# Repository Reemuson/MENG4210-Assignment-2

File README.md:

<h1 align="center">INPUT PROTECTION</h1>

<p align="center" width="100%">
  
</p>

***

<p align="center">
  
&nbsp; &nbsp; &nbsp; &nbsp;
  
</p>

***

## SPECIFICATIONS

| Parameter | Value | 
| --- | --- |
| Dimensions | 50.0 × 50.0 mm |

***

## DIRECTORY STRUCTURE

    .
    ├─ Computations       # Misc calculations
    ├─ HTML               # HTML files for generated webpage
    ├─ Images             # Pictures and renders
    │
    ├─ kibot_resources    # External resources for KiBot
    │  ├─ colors          # Color theme for KiCad
    │  ├─ fonts           # Fonts used in the project
    │  ├─ scripts         # External scripts used with KiBot
    │  └─ templates       # Templates for KiBot generated reports
    │
    ├─ kibot_yaml         # KiBot YAML config files
    ├─ KiRI               # KiRI (PCB diff viewer) files
    │
    ├─ lib                # KiCad footprint and symbol libraries
    │  ├─ 3d_models       # Component 3D models
    │  ├─ lib_fp          # Footprint libraries
    │  └─ lib_sym         # Symbol libraries
    │
    ├─ Logos              # Logos
    │
    ├─ Manufacturing      # Assembly and fabrication documents
    │  ├─ Assembly        # Assembly documents (BoM, pos, notes)
    │  │
    │  └─ Fabrication     # Fabrication documents (ZIP, notes)
    │     ├─ Drill Tables # CSV drill tables
    │     └─ Gerbers      # Gerbers
    │
    ├─ Report             # Reports for ERC/DRC
    ├─ Schematic          # PDF of schematic
    ├─ Templates          # Title block templates
    ├─ Testing
    │  └─ Testpoints      # Testpoints tables      
    │
    └─ Variants           # Outputs for assembly variants

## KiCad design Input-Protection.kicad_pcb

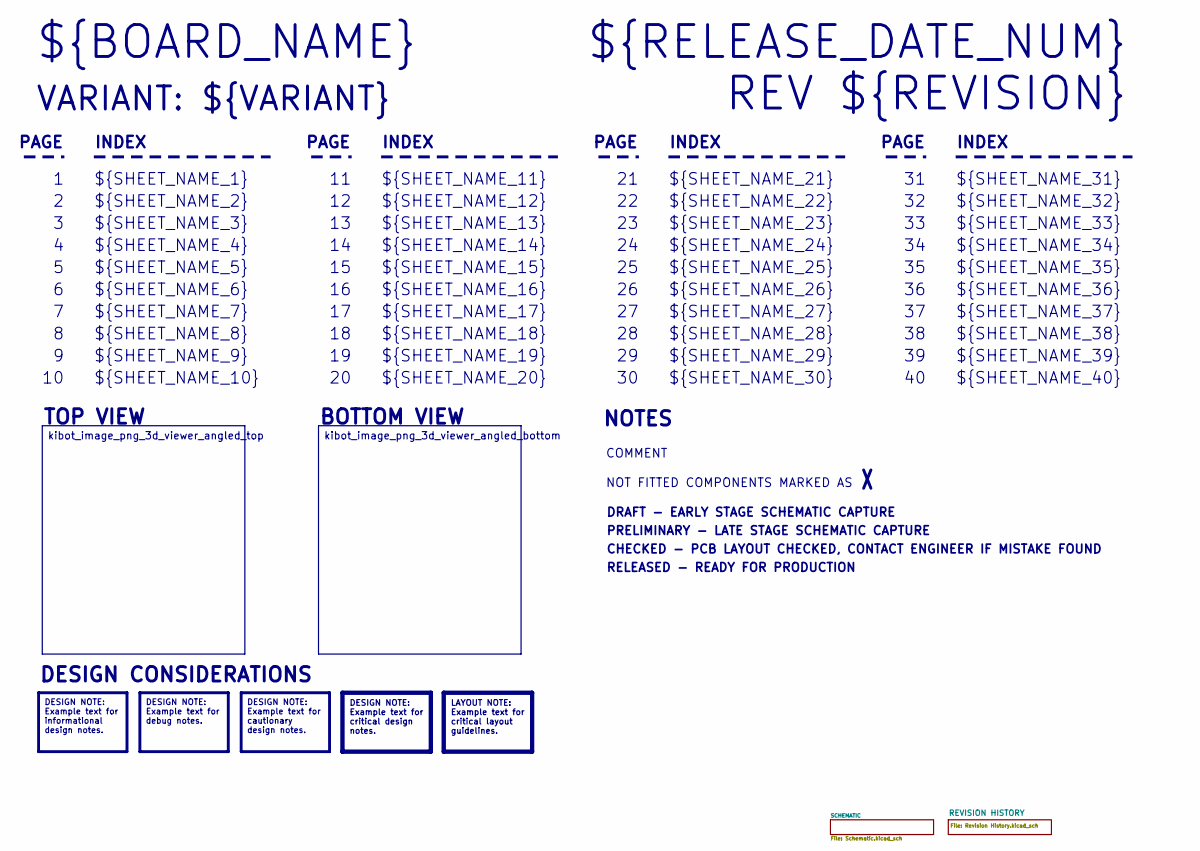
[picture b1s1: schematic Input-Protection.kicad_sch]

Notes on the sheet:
VARIANT: ${VARIANT}
${SHEET_NAME_24}
INDEX
PAGE
${SHEET_NAME_22}
DRAFT - EARLY STAGE SCHEMATIC CAPTURE
${SHEET_NAME_12}
${SHEET_NAME_8}
${SHEET_NAME_2}
${SHEET_NAME_5}
${SHEET_NAME_20}
${SHEET_NAME_23}
${RELEASE_DATE_NUM}
${SHEET_NAME_35}
${SHEET_NAME_11}
CHECKED - PCB LAYOUT CHECKED, CONTACT ENGINEER IF MISTAKE FOUND
${SHEET_NAME_6}
${SHEET_NAME_37}
NOT FITTED COMPONENTS MARKED AS
${SHEET_NAME_26}
${SHEET_NAME_36}
REV ${REVISION}
${SHEET_NAME_15}
BOTTOM VIEW
${SHEET_NAME_14}
${SHEET_NAME_21}
${SHEET_NAME_17}
${SHEET_NAME_18}
${SHEET_NAME_7}
${SHEET_NAME_31}
${BOARD_NAME}
NOTES
${SHEET_NAME_40}
${SHEET_NAME_39}
${SHEET_NAME_32}
${SHEET_NAME_1}
${SHEET_NAME_9}
${SHEET_NAME_38}
${SHEET_NAME_29}
RELEASED - READY FOR PRODUCTION

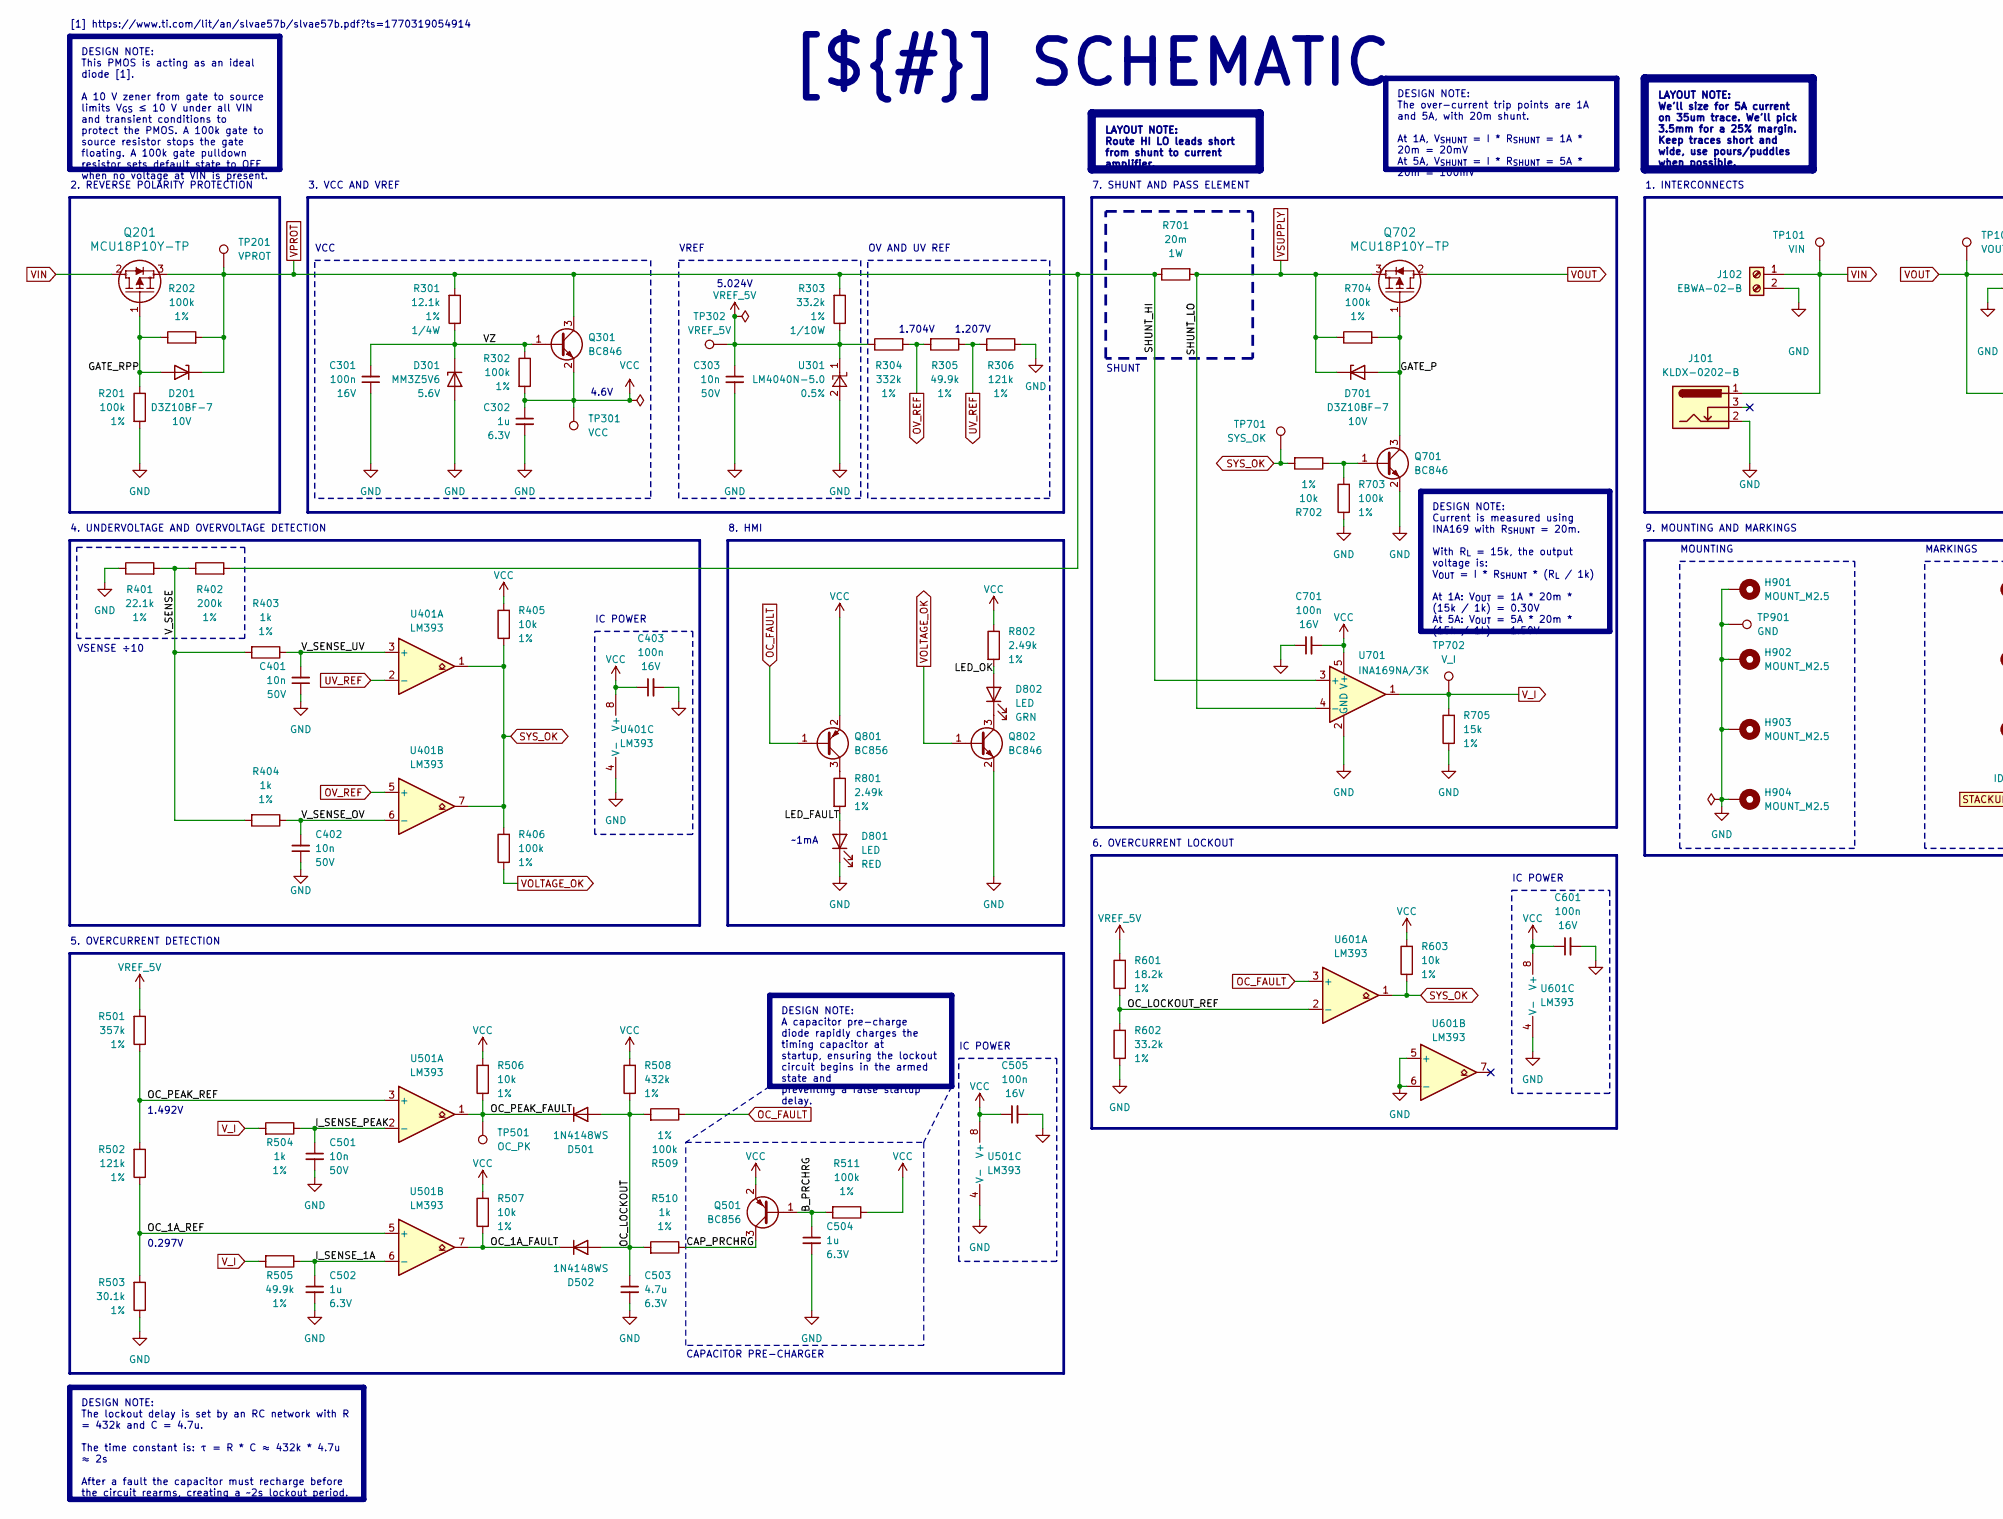
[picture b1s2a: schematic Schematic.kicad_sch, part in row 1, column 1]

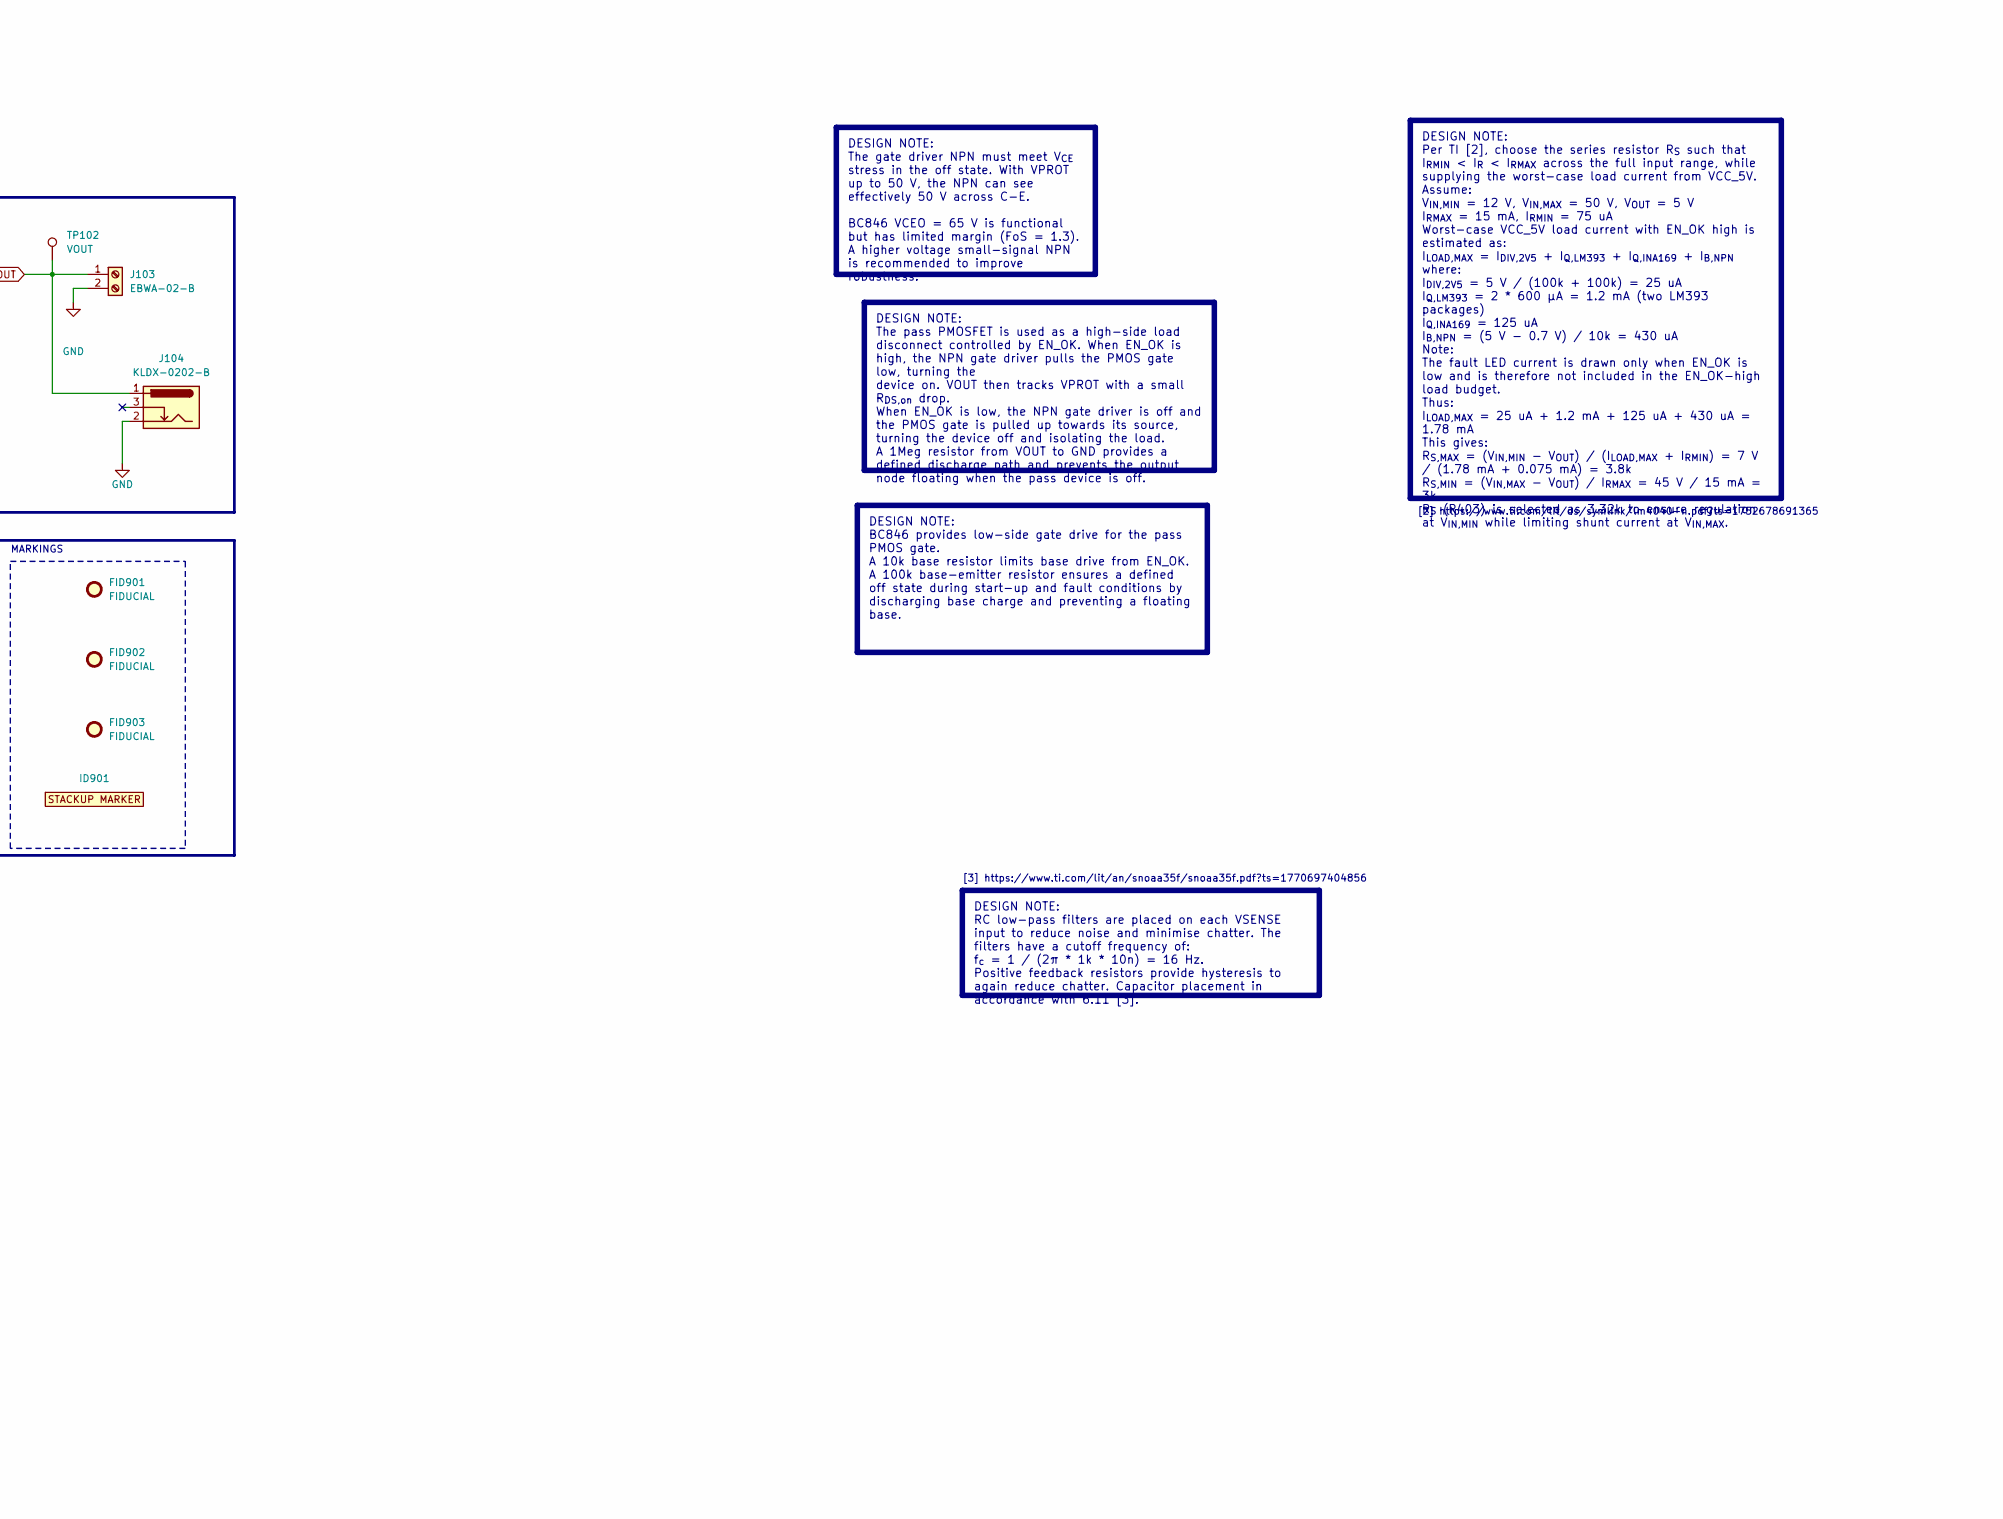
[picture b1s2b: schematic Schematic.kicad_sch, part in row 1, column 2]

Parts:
C301, C403, C505, C601, C701: 100n; C_0603_1608Metric; Voltage_Rating 16V; Tolerance 10%; MPN C1608X7R1C104KT
C302, C502, C504: 1u; C_0603_1608Metric; Voltage_Rating 6.3V; Tolerance 10%; MPN C1608X5R0J105KT
C303, C401, C402, C501: 10n; C_0603_1608Metric; Voltage_Rating 50V; Tolerance 10%; MPN C1608X7R1H103KT
C503: 4.7u; C_0603_1608Metric; Voltage_Rating 6.3V; Tolerance 10%; MPN C1608X5R0J475MT
D201, D701: D3Z10BF-7; D_SOD-323; MPN D3Z10BF-7
D301: MM3Z5V6; D_SOD-323; MPN MM3Z5V6
D501, D502: 1N4148WS; D_SOD-323; MPN 1N4148WS
D801: LED; LED_0805_2012Metric; MPN LTST-C170KRKT
D802: LED; LED_0805_2012Metric; MPN LTST-C170KGKT
FID901, FID902, FID903: FIDUCIAL; Fiducial_1mm_Mask2mm
H901, H902, H903, H904: MOUNT_M2.5; MountingHole_2.7mm_M2.5_ISO7380_Pad
ID901: BOARD_STACKUP_MARKER; STACKUP_ID_2L
J101, J104: KLDX-0202-B; BarrelJack_Kycon_KLDX-0202-xC_Horizontal; MPN KLDX-0202-B
J102, J103: EBWA-02-B; TerminalBlock_Phoenix_MKDS-1-2-3.81_1x02_P3.81mm_Horizontal; MPN EBWA-02-B
Q201, Q702: MCU18P10Y-TP; DPAK_MCC; MPN MCU18P10Y-TP
Q301, Q701, Q802: BC846; SOT-23; MPN BC846
Q501, Q801: BC856; SOT-23
R201, R202, R302, R406, R509, R511, R703, R704: 100k; R_0603_1608Metric; Tolerance 1%
R301: 12.1k; R_1206_3216Metric; Tolerance 1%
R303, R602: 33.2k; R_0603_1608Metric; Tolerance 1%
R304: 332k; R_0603_1608Metric; Tolerance 1%
R305, R505: 49.9k; R_0603_1608Metric; Tolerance 1%
R306, R502: 121k; R_0603_1608Metric; Tolerance 1%
R401: 22.1k; R_0603_1608Metric; Tolerance 1%
R402: 200k; R_0603_1608Metric; Tolerance 1%
R403, R404, R504, R510: 1k; R_0603_1608Metric; Tolerance 1%
R405, R506, R507, R603, R702: 10k; R_0603_1608Metric; Tolerance 1%
R501: 357k; R_0603_1608Metric; Tolerance 1%
R503: 30.1k; R_0603_1608Metric; Tolerance 1%
R508: 432k; R_0603_1608Metric; Tolerance 1%
R601: 18.2k; R_0603_1608Metric; Tolerance 1%
R701: 20m; R_2512_6332Metric; Tolerance 1%; MPN WSL2512R0200FEA
R705: 15k; R_0603_1608Metric; Tolerance 1%
R801, R802: 2.49k; R_0603_1608Metric; Tolerance 1%
TP101: VIN; TestPoint_Pad_D1.0mm
TP102: VOUT; TestPoint_Pad_D1.0mm
TP201: VPROT; TestPoint_Pad_D1.0mm
TP301: VCC; TestPoint_Pad_D1.0mm
TP302: VREF_5V; TestPoint_Pad_D1.0mm
TP501: OC_PK; TestPoint_Pad_D1.0mm
TP701: SYS_OK; TestPoint_Pad_D1.0mm
TP702: V_I; TestPoint_Pad_D1.0mm
TP901: GND; TestPoint_Pad_1.0x1.0mm
U301: LM4040N-5.0; SOT-23; Tolerance 0.5%; MPN LM4040CIM3-5.0/NOPB
U401, U501, U601: LM393; SOIC-8_3.9x4.9mm_P1.27mm
U701: INA169NA/3K; SOT-23-5; MPN INA169NA/3K

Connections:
/SCHEMATIC/B_PRCHRG: C504.1, Q501.1 (B), R511.2
/SCHEMATIC/CAP_PRCHRG: Q501.3 (C), R510.1
/SCHEMATIC/GATE_P: D701.2 (A), Q701.3 (C), Q702.1, R704.2
/SCHEMATIC/GATE_RPP: D201.2 (A), Q201.1, R201.1, R202.1
/SCHEMATIC/I_SENSE_1A: C502.1, R505.1, U501.6 (-)
/SCHEMATIC/I_SENSE_PEAK: C501.1, R504.1, U501.2 (-)
/SCHEMATIC/LED_FAULT: D801.2 (A), R801.2
/SCHEMATIC/LED_OK: D802.2 (A), R802.2
/SCHEMATIC/OC_1A_FAULT: D502.1 (K), R507.1, U501.7
/SCHEMATIC/OC_1A_REF: R502.1, R503.2, U501.5 (+)
/SCHEMATIC/OC_LOCKOUT: C503.1, D501.2 (A), D502.2 (A), R508.1, R509.2, R510.2
/SCHEMATIC/OC_LOCKOUT_REF: R601.1, R602.2, U601.2 (-)
/SCHEMATIC/OC_PEAK_FAULT: D501.1 (K), R506.1, TP501.1, U501.1
/SCHEMATIC/OC_PEAK_REF: R501.1, R502.2, U501.3 (+)
/SCHEMATIC/VZ: C301.2, D301.1 (K), Q301.1 (B), R301.1, R302.1
/SCHEMATIC/V_SENSE: R401.2, R402.1, R403.2, R404.2
/SCHEMATIC/V_SENSE_OV: C402.2, R404.1, U401.6 (-)
/SCHEMATIC/V_SENSE_UV: C401.2, R403.1, U401.3 (+)
GND: C301.1, C302.2, C303.2, C401.1, C402.1, C403.2, C501.2, C502.2, C503.2, C504.2, C505.2, C601.2, C701.1, D301.2 (A), D801.1 (K), H901.1, H902.1, H903.1, H904.1, J101.2, J102.2, J103.2, J104.2, Q701.2 (E), Q802.2 (E), R201.2, R306.1, R401.1, R503.1, R602.1, R703.1, R705.1, TP901.1, U301.2 (A), U401.4 (V-), U501.4 (V-), U601.4 (V-), U601.5 (+), U601.6 (-), U701.2 (GND)
unnamed: D802.1 (K), Q802.3 (C)
unnamed: Q701.1 (B), R702.1, R703.2
unnamed: Q801.3 (C), R801.1
OC_FAULT: Q801.1 (B), R509.1, U601.3 (+)
OV_REF: R304.2, R305.2, U401.5 (+)
SYS_OK: R405.1, R406.2, R603.1, R702.2, TP701.1, U401.1, U401.7, U601.1
UV_REF: R305.1, R306.2, U401.2 (-)
VCC: C302.1, C403.1, C505.1, C601.1, C701.2, Q301.2 (E), Q501.2 (E), Q801.2 (E), R302.2, R405.2, R506.2, R507.2, R508.2, R511.1, R603.2, R802.1, TP301.1, U401.8 (V+), U501.8 (V+), U601.8 (V+), U701.5 (V+)
VIN: J101.1, J102.1, Q201.2, TP101.1
VOLTAGE_OK: Q802.1 (B), R406.1
VOUT: J103.1, J104.1, Q702.2, TP102.1
VPROT: D201.1 (K), Q201.3, Q301.3 (C), R202.2, R301.2, R303.2, R402.2, R701.1, TP201.1, U701.3 (+)
VREF_5V: C303.1, R303.1, R304.1, R501.2, R601.2, TP302.1, U301.1 (K)
VSUPPLY: D701.1 (K), Q702.3, R701.2, R704.1, U701.4 (-)
V_I: R504.2, R505.2, R705.2, TP702.1, U701.1

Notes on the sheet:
SHUNT
[1] https://www.ti.com/lit/an/slvae57b/slvae57b.pdf?ts=1770319054914
~1mA
OV AND UV REF
CAPACITOR PRE-CHARGER
6. OVERCURRENT LOCKOUT
[3] https://www.ti.com/lit/an/snoaa35f/snoaa35f.pdf?ts=1770697404856
IC POWER
8. HMI
3. VCC AND VREF
1.207V
2. REVERSE POLARITY PROTECTION
4. UNDERVOLTAGE AND OVERVOLTAGE DETECTION
[2] https://www.ti.com/lit/ds/symlink/lm4040-n.pdf?ts=1752678691365
0.297V
VREF
VCC
1. INTERCONNECTS
1.704V
VSENSE ÷10
7. SHUNT AND PASS ELEMENT
1.492V
5.024V
4.6V
5. OVERCURRENT DETECTION
MOUNTING
MARKINGS
9. MOUNTING AND MARKINGS
[${#}] ${TITLE}
DESIGN NOTE: The pass PMOSFET is used as a high-side load disconnect controlled by EN_OK. When EN_OK is high, the NPN gate driver pulls the PMOS gate low, turning the device on. VOUT then tracks VPROT with a small R_{DS,on} drop. When EN_OK is low, the NPN gate driver is off and the PMOS gate is pu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
DESIGN NOTE: The over-current trip points are 1A and 5A, with 20m shunt. At 1A, V_{SHUNT} = I * R_{SHUNT} = 1A * 20m = 20mV At 5A, V_{SHUNT} = I * R_{SHUNT} = 5A * 20m = 100mV
DESIGN NOTE: The gate driver NPN must meet V_{CE} stress in the off state. With VPROT up to 50 V, the NPN can see effectively 50 V across C-E. BC846 VCEO = 65 V is functional but has limited margin (FoS = 1.3). A higher voltage small-signal NPN is recommended to improve robustness.
DESIGN NOTE: BC846 provides low-side gate drive for the pass PMOS gate. A 10k base resistor limits base drive from EN_OK. A 100k base-emitter resistor ensures a defined off state during start-up and fault conditions by discharging base charge and preventing a floating base.
DESIGN NOTE: This PMOS is acting as an ideal diode [1]. A 10 V zener from gate to source limits V_{GS} ≤ 10 V under all VIN and transient conditions to protect the PMOS. A 100k gate to source resistor stops the gate floating. A 100k gate pulldown resistor sets default state to OFF when no voltage a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
LAYOUT NOTE: We'll size for 5A current on 35um trace. We'll pick 3.5mm for a 25% margin. Keep traces short and wide, use pours/puddles when possible.
DESIGN NOTE: Current is measured using INA169 with R_{SHUNT} = 20m. With R_{L} = 15k, the output voltage is: V_{OUT} = I * R_{SHUNT} * (R_{L} / 1k) At 1A: V_{OUT} = 1A * 20m * (15k / 1k) = 0.30V At 5A: V_{OUT} = 5A * 20m * (15k / 1k) = 1.50V
DESIGN NOTE: The lockout delay is set by an RC network with R = 432k and C = 4.7u. The time constant is: τ = R * C ≈ 432k * 4.7u ≈ 2s After a fault the capacitor must recharge before the circuit rearms, creating a ~2s lockout period.
DESIGN NOTE: A capacitor pre-charge diode rapidly charges the timing capacitor at startup, ensuring the lockout circuit begins in the armed state and preventing a false startup delay.
LAYOUT NOTE: Route HI LO leads short from shunt to current amplifier.
DESIGN NOTE: Per TI [2], choose the series resistor R_{S} such that I_{RMIN} < I_{R} < I_{RMAX} across the full input range, while supplying the worst-case load current from VCC_5V. Assume: V_{IN,MIN} = 12 V, V_{IN,MAX} = 50 V, V_{OUT} = 5 V I_{RMAX} = 15 mA, I_{RMIN} = 75 uA Worst-case VCC_5V load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

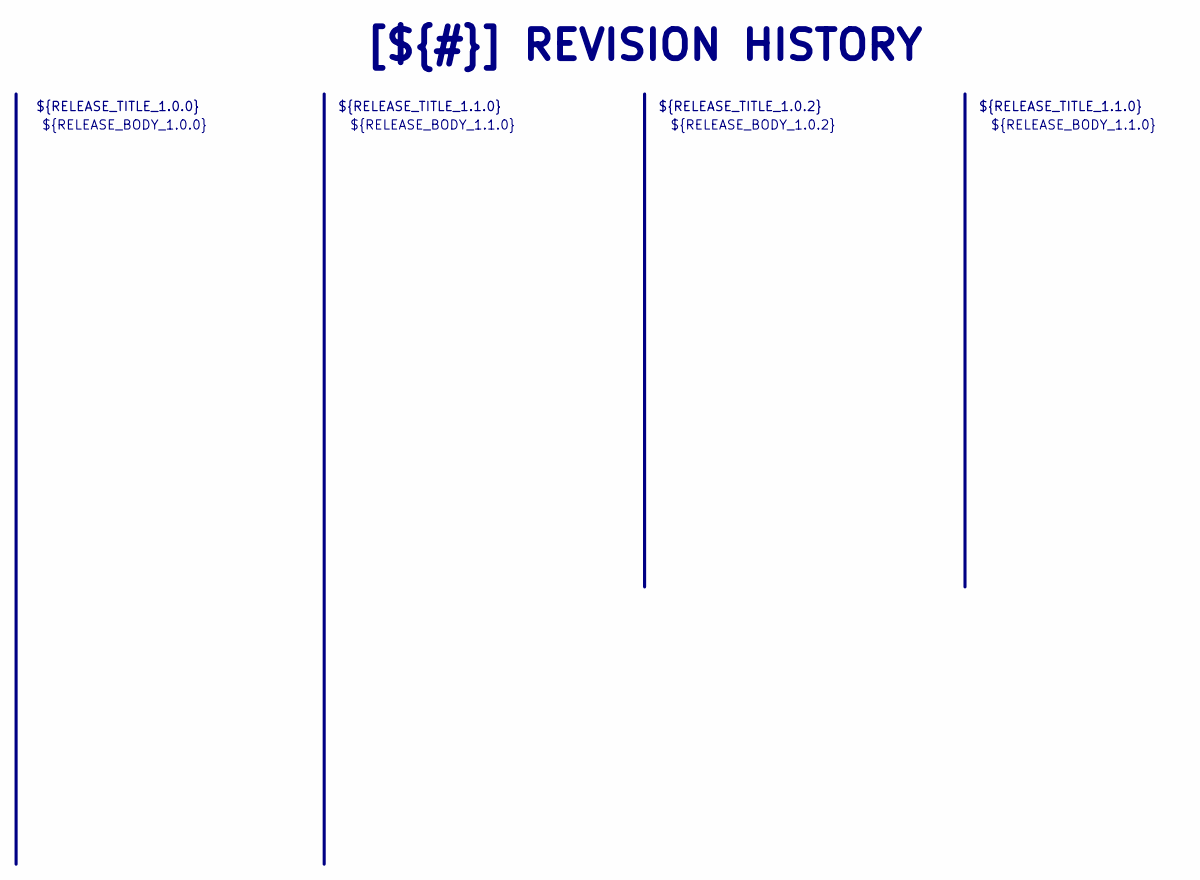
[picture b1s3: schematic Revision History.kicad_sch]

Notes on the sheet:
${RELEASE_BODY_1.1.0}
[${#}] ${TITLE}
${RELEASE_BODY_1.0.0}
${RELEASE_TITLE_1.0.2}
${RELEASE_BODY_1.0.2}
${RELEASE_TITLE_1.0.0}
${RELEASE_TITLE_1.1.0}

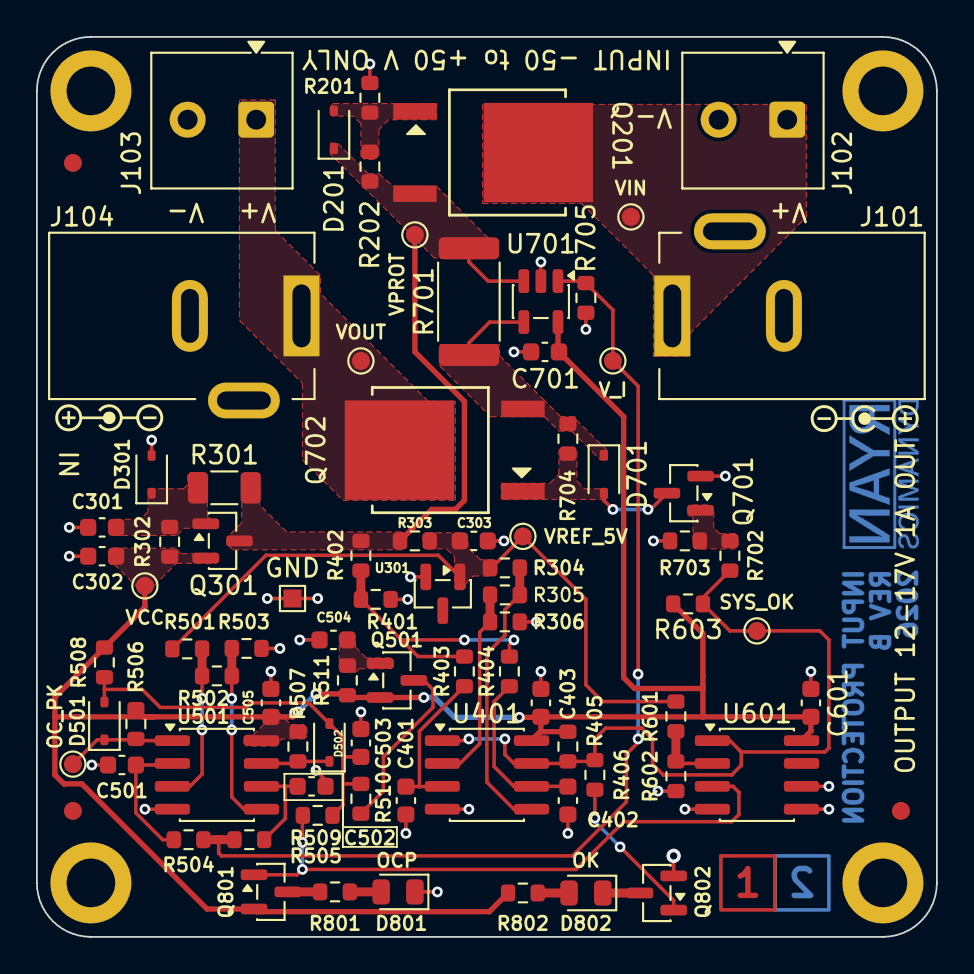
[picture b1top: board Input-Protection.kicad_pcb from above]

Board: 2 copper layers, 50.0 x 50.0 mm, 88 parts (0 on the bottom side), 34 nets.

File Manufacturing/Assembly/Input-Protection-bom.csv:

Row,Quantity Per PCB,References,Value,Datasheet,Footprint,Description,Manufacturer,MPN,Supplier,SPN,Notes
1,4,C303 C401 C402 C501,10n,https://mm.digikey.com/Volume0/opasdata/d220001/medias/docus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,C_0603_1608Metric,CAP CER 0.01UF 50V X7R 0603,TPK,C1608X7R1H103KT,,,
2,5,C301 C403 C505 C601 C701,100n,https://mm.digikey.com/Volume0/opasdata/d220001/medias/docus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,C_0603_1608Metric,CAP CER 0.1UF 16V X7R 0603,TPK,C1608X7R1C104KT,,,
3,3,C302 C502 C504,1u,https://mm.digikey.com/Volume0/opasdata/d220001/medias/docus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,C_0603_1608Metric,CAP CER 1UF 6.3V X7R 0603,TPK,C1608X5R0J105KT,,,
4,1,C503,4.7u,https://mm.digikey.com/Volume0/opasdata/d220001/medias/docus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,C_0603_1608Metric,CAP CER 4.7UF 6.3V X5R 0603,TPK,C1608X5R0J475MT,,,
5,2,D501 D502,1N4148WS,https://diotec.com/request/datasheet/1n4148ws.pdf,D_SOD-323,DIODE STANDARD 75V 150MA SOD323F,Diotec Semiconductor,1N4148WS,,,Fast switching diode
6,2,D201 D701,D3Z10BF-7,https://www.diodes.com/assets/Datasheets/D3ZxVxBF.pdf,D_SOD-323,DIODE ZENER 10V 400MW SOD323F,Diodes Incorporated,D3Z10BF-7,,,"VZ = 10 V, suitable for input over-voltage clamping"
7,1,D801,LED,https://optoelectronics.liteon.com/upload/download/DS-22-99-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,LED_0805_2012Metric,LED RED CLEAR SMD,Lite-On Inc.,LTST-C170KRKT,DigiKey,160-1415-1-ND,Any low power red 0805 LED
8,1,D802,LED,https://optoelectronics.liteon.com/upload/download/DS22-2000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,LED_0805_2012Metric,LED RED CLEAR SMD,Lite-On Inc.,LTST-C170KGKT,DigiKey,160-1414-1-ND,Any low power green 0805 LED
9,1,D301,MM3Z5V6,https://www.diodes.com/assets/Datasheets/D3ZxVxBF.pdf,D_SOD-323,DIODE ZENER 5V6 400MW SOD323F,Diotec,MM3Z5V6,,,"VZ = 5V6, for VCC reference"
10,2,J102 J103,EBWA-02-B,https://app.adam-tech.com/products/download/data_sheet/20424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,TerminalBlock_Phoenix_MKDS-1-2-3.81_1x02_P3.81mm_Horizontal,EURO BLOCK 2P,Adam Tech,EBWA-02-B,,,
11,2,J101 J104,KLDX-0202-B,https://www.kycon.com/Catalog_PDF/KLDX_0202.pdf,BarrelJack_Kycon_KLDX-0202-xC_Horizontal,CONN PWR JACK 2.5X5.5MM SOLDER,Kycon Inc,KLDX-0202-B,,,
12,3,Q301 Q701 Q802,BC846,https://assets.nexperia.com/documents/data-sheet/BC846X-Q_SER.pdf,SOT-23,TRANS NPN 65V 0.1A TO-236AB,Nexperia USA Inc.,BC846,,,"VCEO > 65 V for 50 V rail, IC small, used as gate pull-down switch"
13,2,Q501 Q801,BC856,https://www.onsemi.com/pub/Collateral/BC860-D.pdf,SOT-23,"0.1A Ic, 65V Vce, PNP Transistor, SOT-23",,,,,
14,2,Q201 Q702,MCU18P10Y-TP,https://www.mccsemi.com/pdf/Products/MCU18P10Y(DPAK).pdf,DPAK_MCC,MOSFET P-CH 100V 18A DPAK,MCC (Micro Commercial Components),MCU18P10Y-TP,,,"VDS > 100 V, ID > 2 A, P-channel device suitable for high-side switching"
15,1,R701,20m,https://www.vishay.com/docs/30100/wsl.pdf,R_2512_6332Metric,RES 0.02 OHM 1% 1W 2512,Vishay Dale,WSL2512R0200FEA,DigiKey,WSLG-.02CT-ND,"Current sense shunt, sets OCP trip (~1 A). Ideally should be <100m"
16,4,R403 R404 R504 R510,1k,https://www.analogtechnologies.com/document/New_Resistor_Kits.pdf,R_0603_1608Metric,RES 1K OHM 1% 1/10W 0603,Analog Technologies,,,,
17,2,R801 R802,2.49k,https://www.analogtechnologies.com/document/New_Resistor_Kits.pdf,R_0603_1608Metric,RES 2.49K OHM 1% 1/10W 0603,Analog Technologies,,,,
18,5,R405 R506 R507 R603 R702,10k,https://www.analogtechnologies.com/document/New_Resistor_Kits.pdf,R_0603_1608Metric,RES 10K OHM 1% 1/10W 0603,Analog Technologies,,,,
19,1,R301,12.1k,https://www.analogtechnologies.com/document/New_Resistor_Kits.pdf,R_1206_3216Metric,RES 12.1K OHM 1% 1/4W 1206,Analog Technologies,,,,
20,1,R705,15k,https://www.analogtechnologies.com/document/New_Resistor_Kits.pdf,R_0603_1608Metric,RES 15K OHM 1% 1/10W 0603,Analog Technologies,,,,
21,1,R601,18.2k,https://www.analogtechnologies.com/document/New_Resistor_Kits.pdf,R_0603_1608Metric,RES 18.2K OHM 1% 1/10W 0603,Analog Technologies,,,,
22,1,R401,22.1k,https://www.analogtechnologies.com/document/New_Resistor_Kits.pdf,R_0603_1608Metric,RES 22.1K OHM 1% 1/10W 0603,Analog Technologies,,,,
23,1,R503,30.1k,https://www.analogtechnologies.com/document/New_Resistor_Kits.pdf,R_0603_1608Metric,RES 30.1K OHM 1% 1/10W 0603,Analog Technologies,,,,
24,2,R303 R602,33.2k,https://www.analogtechnologies.com/document/New_Resistor_Kits.pdf,R_0603_1608Metric,RES 33.2K OHM 1% 1/10W 0603,Analog Technologies,,,,
25,2,R305 R505,49.9k,https://www.analogtechnologies.com/document/New_Resistor_Kits.pdf,R_0603_1608Metric,RES 49.9K OHM 1% 1/10W 0603,Analog Technologies,,,,
26,8,R201 R202 R302 R406 R509 R511 R703 R704,100k,https://www.analogtechnologies.com/document/New_Resistor_Kits.pdf,R_0603_1608Metric,RES 100K OHM 1% 1/10W 0603,Analog Technologies,,,,
27,2,R306 R502,121k,https://www.analogtechnologies.com/document/New_Resistor_Kits.pdf,R_0603_1608Metric,RES 121K OHM 1% 1/10W 0603,Analog Technologies,,,,
28,1,R402,200k,https://www.analogtechnologies.com/document/New_Resistor_Kits.pdf,R_0603_1608Metric,RES 200K OHM 1% 1/10W 0603,Analog Technologies,,,,
29,1,R304,332k,https://www.analogtechnologies.com/document/New_Resistor_Kits.pdf,R_0603_1608Metric,RES 332K OHM 1% 1/10W 0603,Analog Technologies,,,,
30,1,R501,357k,https://www.analogtechnologies.com/document/New_Resistor_Kits.pdf,R_0603_1608Metric,RES 357K OHM 1% 1/10W 0603,Analog Technologies,,,,
31,1,R508,432k,https://www.analogtechnologies.com/document/New_Resistor_Kits.pdf,R_0603_1608Metric,RES 432K OHM 1% 1/10W 0603,Analog Technologies,,,,
32,1,U701,INA169NA/3K,http://www.ti.com/lit/ds/symlink/ina169.pdf,SOT-23-5,IC CURRENT MONITOR 0.5% SOT23-5,Texas Instruments,INA169NA/3K,,,Transconductance of 1mA/V
33,3,U401 U501 U601,LM393,http://www.ti.com/lit/ds/symlink/lm393.pdf,SOIC-8_3.9x4.9mm_P1.27mm,"Low-Power, Low-Offset Voltage, Dual Comparators, DIP-8/SOIC-8/TO-99-8",,,,,
34,1,U301,LM4040N-5.0,http://www.ti.com/lit/ds/symlink/lm4040-n.pdf,SOT-23,IC VREF SHUNT 0.5% SOT23-3,Texas Instruments,LM4040CIM3-5.0/NOPB,,,"VREF = 5.0 V, low temperature coefficient, suitable for precision threshold VREF"

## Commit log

2026-02-18 feat: initial commit, assignment 1 base design to be improved
2026-02-18 Update Outputs
2026-03-06 feat: pcb mvp
2026-03-06 Update CHANGELOG
2026-03-06 Update Outputs (release)
